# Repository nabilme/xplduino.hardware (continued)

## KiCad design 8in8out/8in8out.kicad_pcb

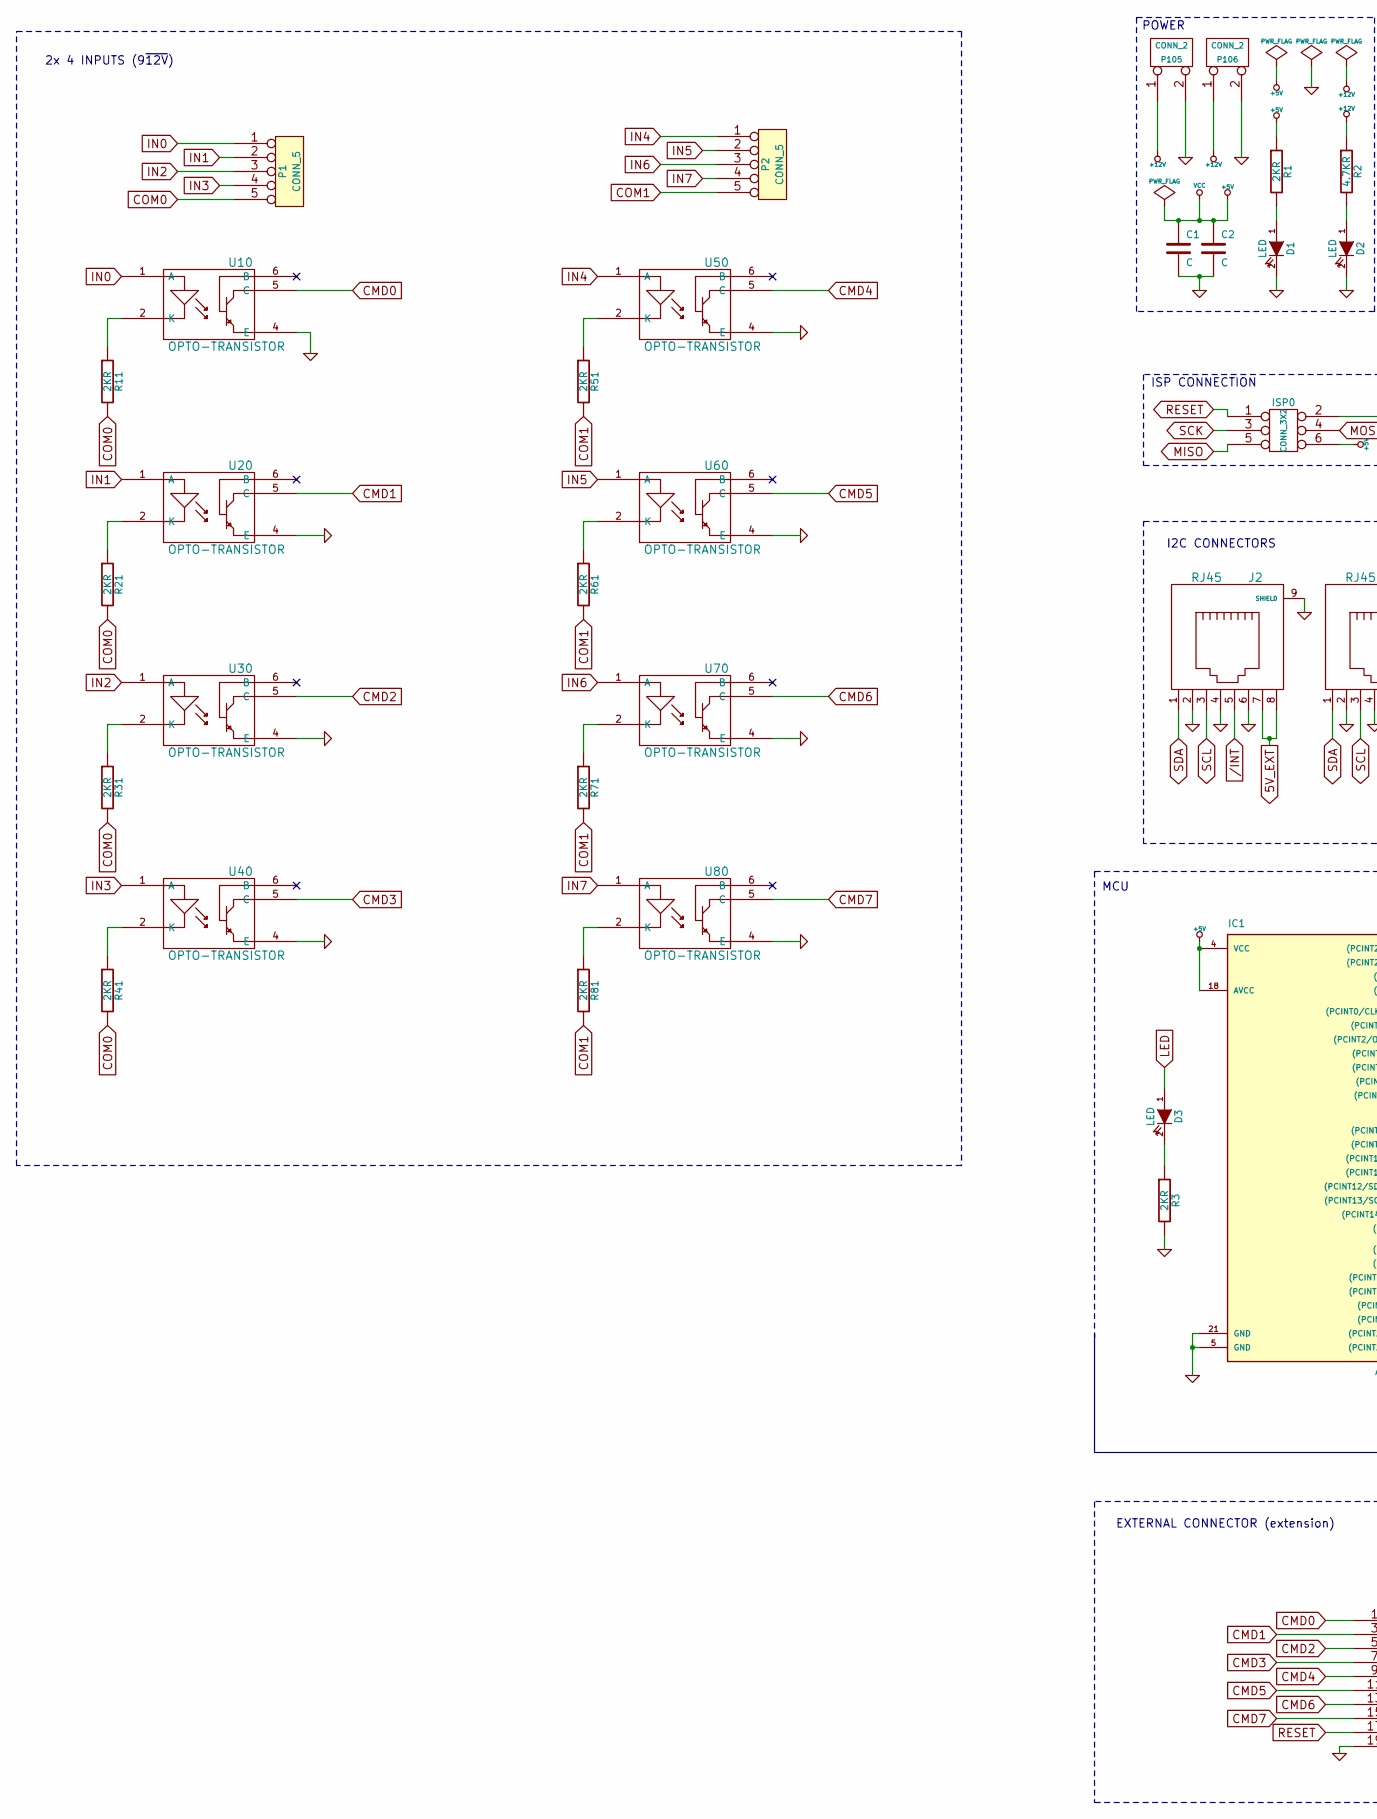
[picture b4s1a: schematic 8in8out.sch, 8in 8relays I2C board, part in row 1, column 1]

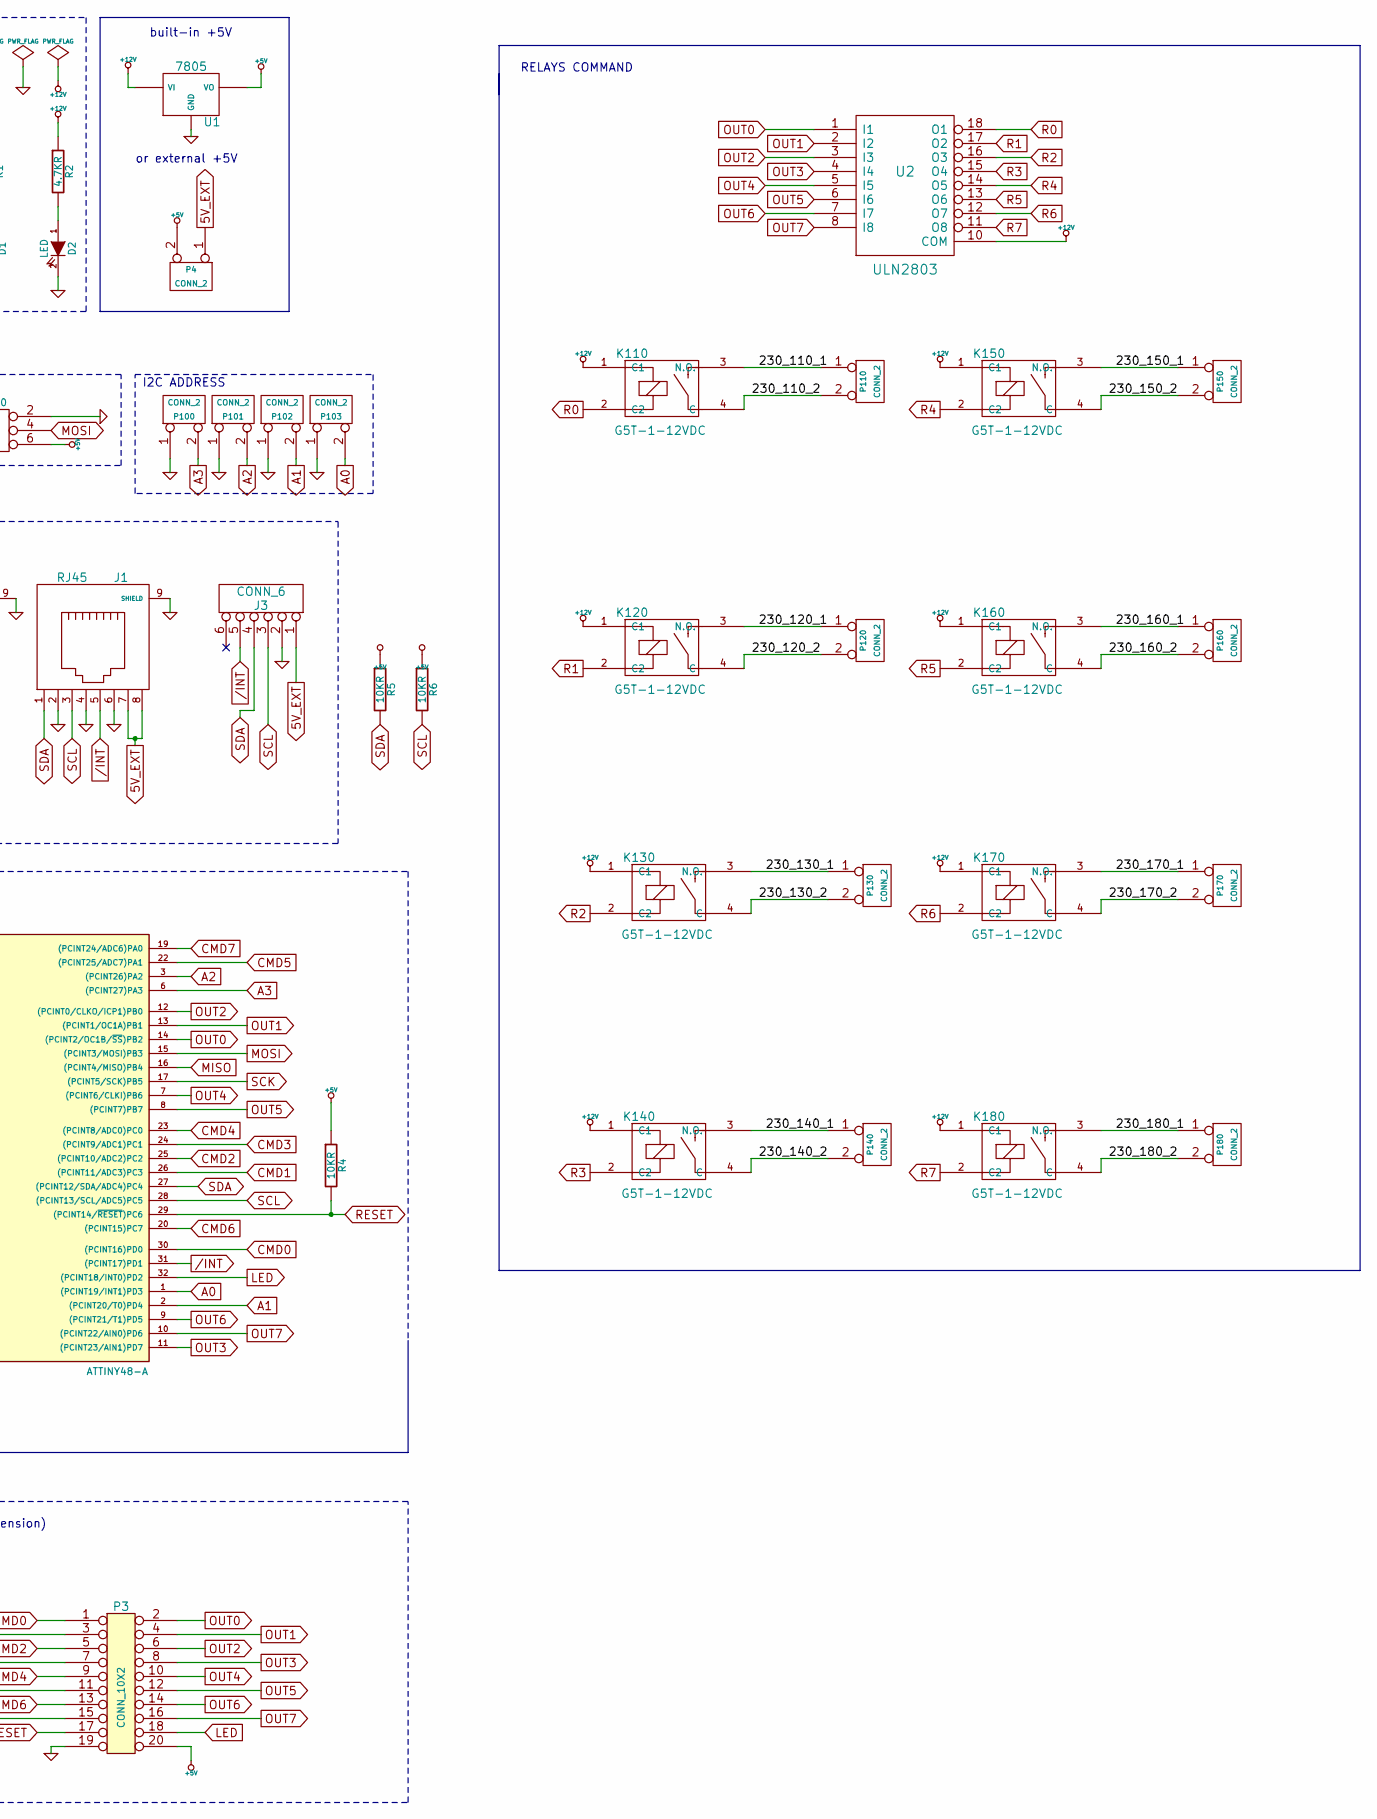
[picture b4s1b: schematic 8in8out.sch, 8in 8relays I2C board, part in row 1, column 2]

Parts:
C1, C2: C
D1, D2, D3: LED
IC1: ATTINY48-A; TQFP32
ISP0: CONN_3X2
J1, J2: RJ45
J3: CONN_6
K110, K120, K130, K140, K150, K160, K170, K180: G5T-1-12VDC
P1, P2: CONN_5
P3: CONN_10X2
P4, P100, P101, P102, P103, P105, P106, P110, P120, P130, P140, P150, P160, P170, P180: CONN_2
R1, R3, R11, R21, R31, R41, R51, R61, R71, R81: 2KR
R2: 4.7KR
R4, R5, R6: 10KR
U1: 7805
U2: ULN2803
U10, U20, U30, U40, U50, U60, U70, U80: OPTO-TRANSISTOR

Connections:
5V_EXT: J1.7, J1.8, J2.7, J2.8, J3.1, P4.1
+5V: C1.1, C2.1, IC1.4 (VCC), IC1.18 (AVCC), ISP0.6, P3.20, P4.2 (PM), R1.1, R4.1, R5.1, R6.1, U1.VO
+12V: K110.1 (C1), K120.1 (C1), K130.1 (C1), K140.1 (C1), K150.1 (C1), K160.1 (C1), K170.1 (C1), K180.1 (C1), P105.1, P106.1, R2.1, U1.VI, U2.10 (COM)
/230_110_1: K110.3 (N.O.), P110.1
/230_110_2: K110.4 (C), P110.2 (PM)
/230_120_1: K120.3 (N.O.), P120.1
/230_120_2: K120.4 (C), P120.2 (PM)
/230_130_1: K130.3 (N.O.), P130.1
/230_130_2: K130.4 (C), P130.2 (PM)
/230_140_1: K140.3 (N.O.), P140.1
/230_140_2: K140.4 (C), P140.2 (PM)
/230_150_1: K150.3 (N.O.), P150.1
/230_150_2: K150.4 (C), P150.2 (PM)
/230_160_1: K160.3 (N.O.), P160.1
/230_160_2: K160.4 (C), P160.2 (PM)
/230_170_1: K170.3 (N.O.), P170.1
/230_170_2: K170.4 (C), P170.2 (PM)
/230_180_1: K180.3 (N.O.), P180.1
/230_180_2: K180.4 (C), P180.2 (PM)
/INT: IC1.31 ((PCINT17)PD1), J1.5, J2.5, J3.5
A0: IC1.1 ((PCINT19/INT1)PD3), P103.2 (PM)
A1: IC1.2 ((PCINT20/T0)PD4), P102.2 (PM)
A2: IC1.3 ((PCINT26)PA2), P101.2 (PM)
A3: IC1.6 ((PCINT27)PA3), P100.2 (PM)
CMD0: IC1.30 ((PCINT16)PD0), P3.1, U10.5 (C)
CMD1: IC1.26 ((PCINT11/ADC3)PC3), P3.3, U20.5 (C)
CMD2: IC1.25 ((PCINT10/ADC2)PC2), P3.5, U30.5 (C)
CMD3: IC1.24 ((PCINT9/ADC1)PC1), P3.7, U40.5 (C)
CMD4: IC1.23 ((PCINT8/ADC0)PC0), P3.9, U50.5 (C)
CMD5: IC1.22 ((PCINT25/ADC7)PA1), P3.11, U60.5 (C)
CMD6: IC1.20 ((PCINT15)PC7), P3.13, U70.5 (C)
CMD7: IC1.19 ((PCINT24/ADC6)PA0), P3.15, U80.5 (C)
COM0: P1.5, R11.2, R21.2, R31.2, R41.2
COM1: P2.5, R51.2, R61.2, R71.2, R81.2
GND: C1.2, C2.2, D1.2 (K), D2.2 (K), IC1.5 (GND), IC1.21 (GND), ISP0.2, J1.2, J1.4, J1.6, J1.9 (SHIELD), J2.2, J2.4, J2.6, J2.9 (SHIELD), J3.2, P3.19, P100.1, P101.1, P102.1, P103.1, P105.2 (PM), P106.2 (PM), R3.2, U1.GND, U2.9 (GND), U10.4 (E), U20.4 (E), U30.4 (E), U40.4 (E), U50.4 (E), U60.4 (E), U70.4 (E), U80.4 (E)
IN0: P1.1, U10.1 (A)
IN1: P1.2, U20.1 (A)
IN2: P1.3, U30.1 (A)
IN3: P1.4, U40.1 (A)
IN4: P2.1, U50.1 (A)
IN5: P2.2, U60.1 (A)
IN6: P2.3, U70.1 (A)
IN7: P2.4, U80.1 (A)
LED: D3.1 (A), IC1.32 ((PCINT18/INT0)PD2), P3.18
MISO: IC1.16 ((PCINT4/MISO)PB4), ISP0.5
MOSI: IC1.15 ((PCINT3/MOSI)PB3), ISP0.4
unnamed: R71.1, U70.2 (K)
unnamed: R81.1, U80.2 (K)
unnamed: R51.1, U50.2 (K)
unnamed: R41.1, U40.2 (K)
unnamed: R61.1, U60.2 (K)
unnamed: D3.2 (K), R3.1
unnamed: R11.1, U10.2 (K)
unnamed: R21.1, U20.2 (K)
unnamed: R31.1, U30.2 (K)
unnamed: D2.1 (A), R2.2
unnamed: D1.1 (A), R1.2
OUT0: IC1.14 ((PCINT2/OC1B/~SS~)PB2), P3.2, U2.1 (I1)
OUT1: IC1.13 ((PCINT1/OC1A)PB1), P3.4, U2.2 (I2)
OUT2: IC1.12 ((PCINT0/CLKO/ICP1)PB0), P3.6, U2.3 (I3)
OUT3: IC1.11 ((PCINT23/AIN1)PD7), P3.8, U2.4 (I4)
OUT4: IC1.7 ((PCINT6/CLKI)PB6), P3.10, U2.5 (I5)
OUT5: IC1.8 ((PCINT7)PB7), P3.12, U2.6 (I6)
OUT6: IC1.9 ((PCINT21/T1)PD5), P3.14, U2.7 (I7)
OUT7: IC1.10 ((PCINT22/AIN0)PD6), P3.16, U2.8 (I8)
R0: K110.2 (C2), U2.18 (O1)
R1: K120.2 (C2), U2.17 (O2)
R2: K130.2 (C2), U2.16 (O3)
R3: K140.2 (C2), U2.15 (O4)
R4: K150.2 (C2), U2.14 (O5)
R5: K160.2 (C2), U2.13 (O6)
R6: K170.2 (C2), U2.12 (O7)
R7: K180.2 (C2), U2.11 (O8)
RESET: IC1.29 ((PCINT14/~RESET~)PC6), ISP0.1, P3.17, R4.2
SCK: IC1.17 ((PCINT5/SCK)PB5), ISP0.3
SCL: IC1.28 ((PCINT13/SCL/ADC5)PC5), J1.3, J2.3, J3.3, R6.2
SDA: IC1.27 ((PCINT12/SDA/ADC4)PC4), J1.1, J2.1, J3.4, R5.2

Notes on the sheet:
ISP CONNECTION
I2C ADDRESS
POWER
I2C CONNECTORS
MCU
built-in +5V
or external +5V
RELAYS COMMAND
2x 4 INPUTS (9~12V)
EXTERNAL CONNECTOR (extension)

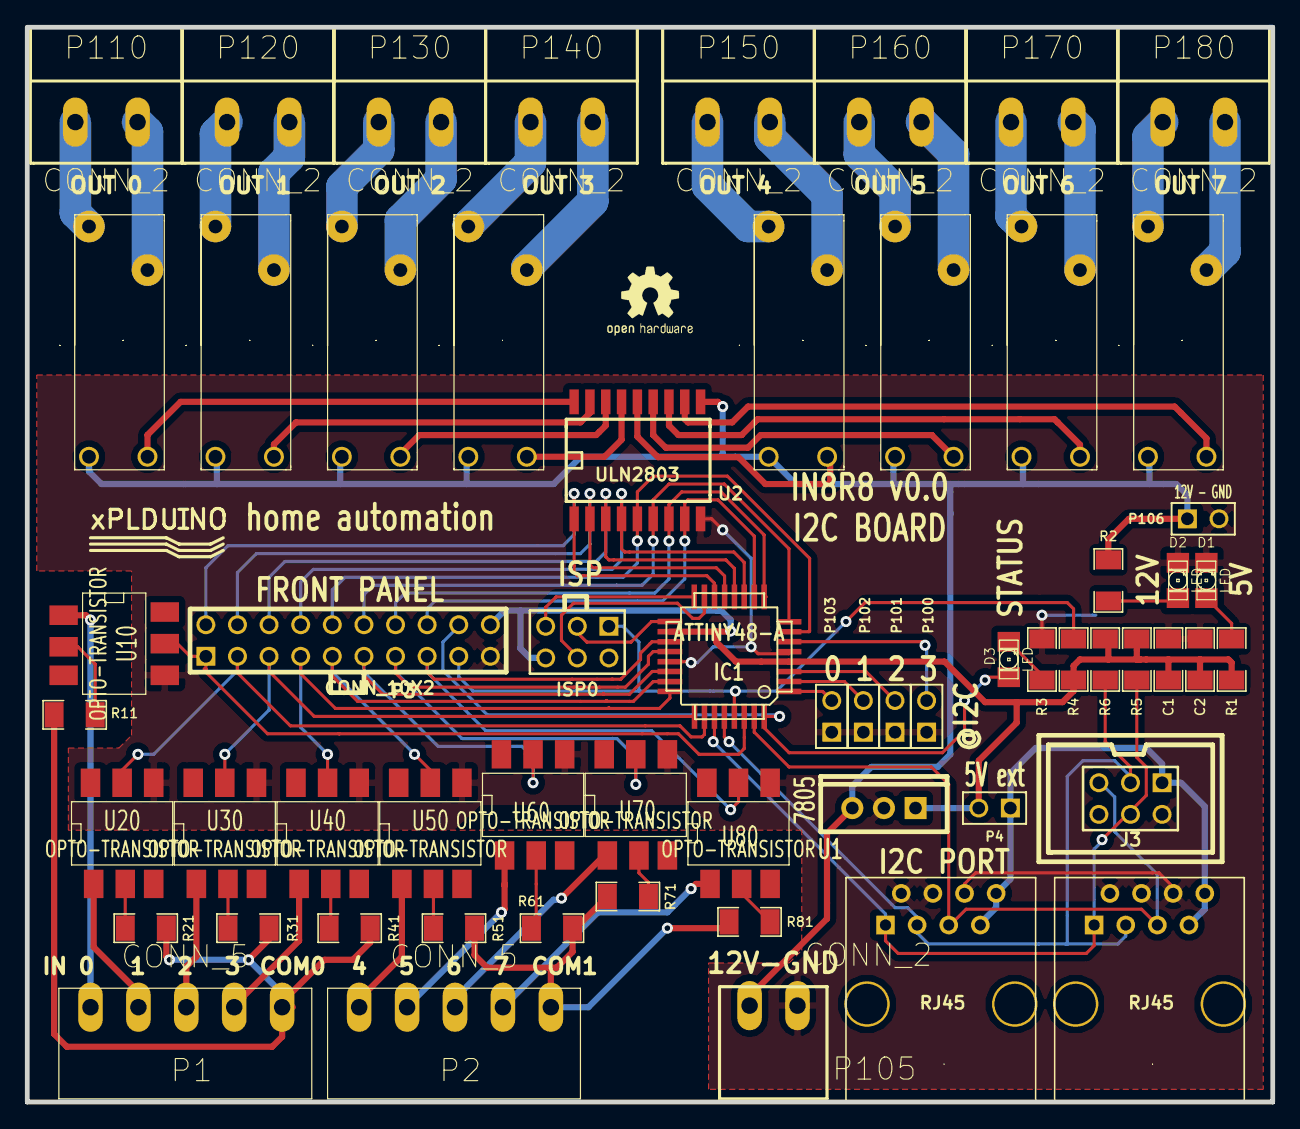
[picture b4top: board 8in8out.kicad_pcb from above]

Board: 2 copper layers, 100.1 x 86.4 mm, 62 parts (0 on the bottom side), 77 nets.

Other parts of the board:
logo_xplduino: VAL**; logo_xplduino
logo_xplduino#2: VAL**; logo_xplduino

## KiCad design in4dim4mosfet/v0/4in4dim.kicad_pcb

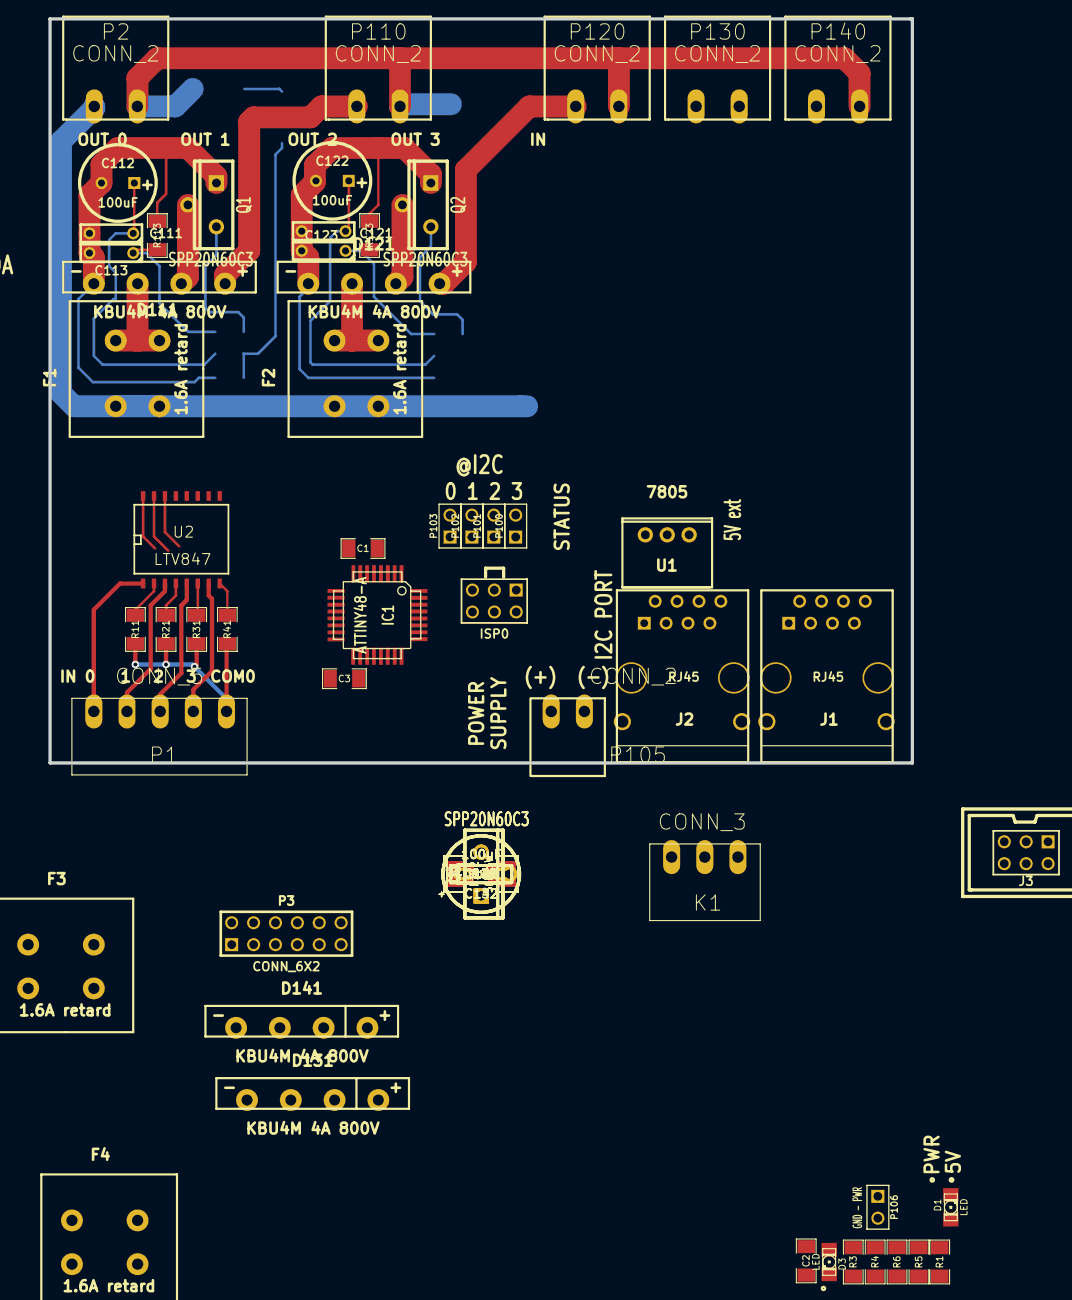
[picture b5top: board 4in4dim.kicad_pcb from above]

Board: 2 copper layers, 100.1 x 86.4 mm, 89 parts (0 on the bottom side), 77 nets.

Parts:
C1, C2: 0.1uF; SM1206
C3: 4.7uF; SM1206
C111, C121, C131, C141: 0.1uF; C2
C112, C122, C132, C142: 100uF; C1.5V8V
C113, C123, C133, C143: 10nF; C2
D1, D3: LED; LED-1206
D111, D121, D131, D141: KBU4M 4A 800V; GBU-4L
D112, D122, D132, D142: 1N5062; SM1206POL
D113, D123, D133, D143: BZX55; SM1206POL
F1, F2, F3, F4: 1.6A retard; FUSEHOLDER_811
GS1: GS2
IC1: ATTINY48-A; TQFP32
ISP0: CONN_3X2; pin_array_3x2
J1, J2: RJ45; RJ45_BASIC
J3: CONN_6; HE10-6
K1: CONN_3; MOL_CONN_3_MINI
P1: CONN_5; MOL_CONN_5_MINI
P2, P110, P120, P130, P140: CONN_2; MOL_CONN_2_H
P3: CONN_6X2; pin_array_6x2
P100, P101, P102, P103, P106: CONN_2; PIN_ARRAY_2X1
P105: CONN_2; MOL_CONN_2_MINI
Q1, Q2, Q3, Q4: SPP20N60C3; TO220_POWERMOSFET_VERT_DEC
R1, R3, R11, R21, R31, R41: 2KR; SM1206
R4, R5, R6: 10KR; SM1206
R16, R17, R18, R19: 310; SM1206
R111, R112, R121, R122, R131, R132, R141, R142: 56K 1W; SM2512
R113, R123, R133, R143: 15K; SM1206
R114, R124, R134, R144: 100R; SM1206
U1: 7805; RECOM
U2, U3: LTV847; SO16W

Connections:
5V_EXT: GS1.2, J1.7, J1.8, J2.7, J2.8, J3.1
+5V: C1.1, C2.1, C3.1, GS1.1, IC1.4, IC1.18, ISP0.2, P3.12, R1.1, R4.1, R5.1, R6.1, U3.1, U3.3, U3.5, U3.7
+12V: P105.1, P106.1
/110D: D111.3, Q1.1
/110L: D111.2, F1.2
/110P: D111.4, P110.2
/110S: C111.2, C112.2, C113.2, D111.1, D113.2, Q1.3, R113.1
/120D: D121.3, Q2.1
/120L: D121.2, F2.2
/120M: D121.4, P120.2
/120S: C121.2, C122.2, C123.2, D121.1, D123.2, Q2.3, R123.1
/130L: D131.2, F3.2
/130M: D131.4, P130.2
/140L: D141.2, F4.2
/140M: D141.4, P140.2
/INT: IC1.23, J1.5, J2.5, J3.5
A0: IC1.1, P103.2
A1: IC1.2, P102.2
A2: IC1.3, P101.2
A3: IC1.6, P100.2
CMD0: IC1.20, P3.1, U2.16
CMD1: IC1.26, P3.3, U2.14
CMD2: IC1.25, P3.5, U2.12
CMD3: IC1.24, P3.7, U2.10
COM0: P1.5, R11.1, R21.1, R31.1, R41.1
GND: C1.2, C2.2, C3.2, D1.2, IC1.5, IC1.21, ISP0.6, J1.2, J1.4, J1.6, J1.9, J2.2, J2.4, J2.6, J2.9, J3.2, K1.3, P3.11, P100.1, P101.1, P102.1, P103.1, P105.2, P106.2, R3.2, U2.9, U2.11, U2.13, U2.15
IN0: P1.1, U2.1
IN1: P1.2, U2.3
IN2: P1.3, U2.5
IN3: P1.4, U2.7
L: F1.1, F2.1, F3.1, F4.1, P2.2
LED: D3.1, IC1.32, P3.10
MISO: IC1.16, ISP0.1
MOSI: IC1.15, ISP0.4
N: P2.1, P110.1, P120.1, P130.1, P140.1, R111.2, R121.2, R131.2, R141.2
unnamed: D112.1, D113.1, R112.1
unnamed: R41.2, U2.8
unnamed: R31.2, U2.6
unnamed: R21.2, U2.4
unnamed: R11.2, U2.2
unnamed: D3.2, R3.1
unnamed: D1.1, R1.2
unnamed: Q4.2, R144.1
unnamed: C141.2, C142.2, C143.2, D141.1, D143.2, Q4.3, R143.1
unnamed: R141.1, R142.2
unnamed: Q1.2, R114.1
unnamed: D142.1, D143.1, R142.1
unnamed: D141.3, Q4.1
unnamed: Q3.2, R134.1
unnamed: D131.3, Q3.1
unnamed: D122.1, D123.1, R122.1
unnamed: D132.1, D133.1, R132.1
unnamed: C131.2, C132.2, C133.2, D131.1, D133.2, Q3.3, R133.1
unnamed: Q2.2, R124.1
unnamed: R121.1, R122.2
unnamed: R111.1, R112.2
unnamed: R131.1, R132.2
unnamed: R16.2, U3.2
unnamed: R17.2, U3.4
unnamed: R18.2, U3.6
unnamed: R19.2, U3.8
OUT0: IC1.8, P3.2, R16.1
OUT0_A: C111.1, C112.1, D112.2, U3.16
OUT0_B: C113.1, R113.2, R114.2, U3.15
OUT1: IC1.7, P3.4, R17.1
OUT1_A: C121.1, C122.1, D122.2, U3.14
OUT1_B: C123.1, R123.2, R124.2, U3.13
OUT2: IC1.9, P3.6, R18.1
OUT2_A: C131.1, C132.1, D132.2, U3.12
OUT2_B: C133.1, R133.2, R134.2, U3.11
OUT3: IC1.10, P3.8, R19.1
OUT3_A: C141.1, C142.1, D142.2, U3.10
OUT3_B: C143.1, R143.2, R144.2, U3.9
RESET: IC1.29, ISP0.5, P3.9, R4.2
SCK: IC1.17, ISP0.3
SCL: IC1.28, J1.3, J2.3, J3.3, R6.2
SDA: IC1.27, J1.1, J2.1, J3.4, R5.2

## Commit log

2012-08-17 First commit of this repository dedicated to hardware. All previous board are availabled: - lin16i2c - lmb (eagle) - lr8i2c - smb
    New board:
    - in4dim4i2c (beta)
2012-08-21 Add zero cross detection circuit and P620 footprint
2012-08-21 routage pcb (suite)
2012-08-23 Add status led Optimize the routing Ready for review
2012-08-27 Changed the support of fuses
2012-08-28 SD and reset button modifications
2012-08-29 Add /spare signal to the pin number 6 of the I2C connector Add silkscreen
2012-08-29 Add selector for the autonomious mode configuration
2012-08-31 Change the footprint of Triac (inverted)
2012-09-05 Add resistor on the command of triacs Add capacitors on power
2012-09-09 Fixed net 65 problem. Should be ready to release ! ;)
2012-09-10 Added temporary 12 volt connector, next version will have a true connector.
2012-09-11 Review.
2012-09-13 Add silkscreen Gerber files generation Modify the pads size of the connector 3 pins
2012-09-13 update cartridge
2012-09-13 Update cartridge Add silkscreen Gerber files generation
2012-09-18 Add draft of dimmer with 230vac inputs
2012-09-19 Dimmer AC: Remove all the pull-up resistors (we will use the internal pull up resistors of the ATTiny)
2012-09-19 Dimmer AC: Add silkscreen Gerber files generation Ready for design review
2012-09-20 Add 230VAC spare connector Change the position of leds inputs Generation of Gerber files
2012-09-21 Move the I2C connectors 2mm lower and 1mm on the left Adjust cartridge description
2012-09-21 The PCB is now larger (5 mm), with line to delimit the cutting position (case of large box)
2012-09-21 Add Gerber files with command number. Ready for fabrication.
2012-09-28 Cr?ation 4in4out : attiny + 4 in + 4 relays (draft)
2012-09-28 Suppression des PNP
2012-09-29 Mise ? jour de la carte 4in4out : Ajout des connecteurs et nommage des composants
2012-09-29 Ajout de capa pour le 5V dans le sch?ma, association des composants avec leur module, cr?ation du module G5T-1-12VDC (Pin a revoir)
2012-09-30 4in4out : Routage Complet (Revoir taille et formes des pistes)
2012-09-30 Ajout du PCB 4in4out
2012-10-01 Mise ? jour du cartouche sur la carte 4in4out
2012-10-02 Refonte du pcb 4in4out
2012-10-03 PCB 4in4out draft apres refonte
2012-10-03 Mise ? jour PCB 4 In 4 out
2012-10-03 4in4out ajout du plan de masse
2012-10-03 Deplacement Resistance led de sortir, mise en place label, am?lioration du plan de masse
2012-10-03 Ajout du logo xplduino, mise ? jour des piste 230V de sortie
2012-10-04 Mise ? jour 4in4out
2012-10-18 Correction of connectors footprint (solar recover bottom layer)
2012-10-18 clean the files removed
2013-02-08 Ajout de la carte 8in/8out Draft
2013-02-08 Mise ? jour Draft
2013-02-09 Ajout 74HC165 sur les entr?es + pull up Creation du connecteur mini 5 poles Debut routage
2013-02-09 ajout de fichiers
2013-02-10 Redimensionnement PCB en 100*86
2013-02-10 Correction pin data du 74HC165 Ajustement position des composants
2013-02-10 Corrected production mistakes. SPI_CLK for ISP, MISO sdcard
2013-02-11 Modification 74HC165
2013-02-11 commit pour merge
2013-02-12 Variante carte 8in 8r sans leds E/S sur la carte Les temoins seront ? d?porter sur une carte additionnelle en face avant
2013-02-13 ajout deux points par relais pour bypasser le NPN et commander le relais en direct (mode secours update .brd
2013-02-13 Mis au propre du sch?ma
2013-02-14 ajout d'un connecteur 12v-Gnd-5v (P200)
2013-04-07 Routage, diverses ameliorations
2013-04-10 Remplacement des transistors et diodes de roues libres par un ULN2803
2013-04-10 reprise plan de masse pour distances de s?cu ajout r?sistances de pullup i2c doublement pistes de puissance 230VAC
2013-04-18 Agrandissement pad des contacts relais Alignement composants Ajout logo
2013-04-19 ajout empreinte boitier
2013-04-19 Changement connecteur 12v par modele 3.85mm
2013-04-25 Creation carte d'extension pour carte 8in8out
2013-04-25 update serigraphie
2013-04-26 Serigraphie
2013-05-01 Deplacement optos et r?sistances cause conflit boitier Serigraphie
2013-05-02 mise ? jour serigraphie
2013-05-02 remplacement leds cms par led 3 mm reamenagement position leds et switchs reprise serigraphie
2013-05-09 Final pour prod
2013-05-13 SMB V0.1 Draft
2013-05-14 modif schema
2013-05-14 Add slot I2C
2013-05-14 SMBV0.1 Mise ? jour Slot TinyRTC + I2C Slot
2013-05-15 Mise ? jour de la SMBV0.1
2013-05-16 SMB V0.1 Update
2013-05-18 gerber files for production
2013-05-18 modification des packages
2013-05-19 Draft PCB SMBV0.1
2013-05-22 routage complet ajout rs485 attention, tous les packages sont ? v?rifier
2013-05-23 routage, reprise plan de masse, suppression de vias
2013-05-23 M?J Piste, Plan de masse, Via
2013-05-29 correction broche 8 du module RS485 + inversion tx+/tx- au niveau du connecteur + pilotage E/R independant inversion polarit? connecteur d'alim d?placement slot pour rtc simplification routage et opt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
2013-06-01 renommage v0.0 en v0.0.TYPEA suite ajout type B
2013-06-01 Creation variante Type B = nouveau type de relais (type panasonic LK-T)
2013-06-01 nettoyage dossier 8in8out
2013-06-02 ajout capa C3
2013-06-02 ajout variante C pour relais type Omron G5SB
2013-06-03 correction empreinte relais (inversion broches du contact) correction empreinte RJ45 (ajout percage shield)
2013-06-03 correction RJ45
2013-06-03 correction RJ45 du port I2C
2013-06-04 correction cablage RJ45 i2c pour etre conforme aux autres cartes 8in8out deplacement de connecteur pour liberer de la place pour les slots
2013-06-06 creation variante D relais ref T77S1D10-12 de chez TE. Existe en 12v et 24v
2013-06-08 ajout gateway onewire DS2482-100 + connecteur 3 points deplacement connecteurs pour amelioration branchement remplacement connecteur 5 points rs485 par 3 points + un strap pour resistance de terminai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
2013-06-08 modif mineure
2013-06-16 ajout trou de fixation reprise connecteur 2x10 pour extension deplacement slot I2C ...
2013-06-16 correction connecteur ISP
2013-06-20 reprise connecteur correction mask back connecteur 230v serigraphie complete double piste relais cot? puissance verification routage generation gerber bon pour fab ?
2013-06-22 correction serigraphie augmentation zone isolation 12v
2013-06-22 generation gerber controle et optimisation routage ajout empreinte TO92 pour ds18b20 ajout i2c sur connecteur d'extension
2013-06-23 suppression pin DS du slot RTC (inutile depuis l'installation d'un DS2408) ajout led 'fault'
2013-06-23 remplacement empreinte 7805 (TO220) par empreinte dc-dc type RECOM boug? connecteur ISP et adresse i2c pour lui laisser de la place
2013-06-25 mis au pas 2.54 ecartement slot i2c inversion connecteur FTDI/leds
2013-06-26 creation d'un support type "shield" pour permettre de personnaliser le circuit mis en place d'un mini connecteur 2 points reli?s au shield serigraphie
2013-06-29 Modification Routage SMB : Connecteur Spare 3 broches avec GND RX1 et TX1 sans via Suppression via sur connexion vers front panel Changement de place des nom pour le connecteur My Shield (Haut) Modif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
2013-06-30 ajout percage rj45 i2c (blindage) retouche routage
2013-06-30 gerber pour fab
2013-06-30 ajout percage rj45 i2c (blindage) gerber pour prod
2013-10-09 creation de la face avant simple de la carte 8in8r: - leds etat E/S, power et status - bouton poussoir reset
2013-10-09 version 0.0 + deplacement opto U10
2013-10-09 deplacement ULN2803 pour degagement connecteur extension
2013-10-09 elargissement ecartement pads CMS6 reprise plan de masse
2013-10-23 correction table adressage modif uln et routage controle ok, gerber ok, pret pour prod
2013-10-23 agrandissement taille du panneau ajout NPN pour commande led status serigraphie
2013-11-21 ?change package SOT23 des transistors: 1.B 2.E 3.C au lieu de 1.E 2.B 3.C
2013-11-28 correction erreur schema led out5 pas reli? au GND
2014-02-28 ajout schema en pdf et gerber
2014-02-28 ajout resistance forcage sortie routage incomplet
2014-03-02 premier commit dimmer power mosfet manque encore le circuit ZC
2014-03-04 amelioration routage partie puissance pour liberer les deux faces pour le passage de la puissance
